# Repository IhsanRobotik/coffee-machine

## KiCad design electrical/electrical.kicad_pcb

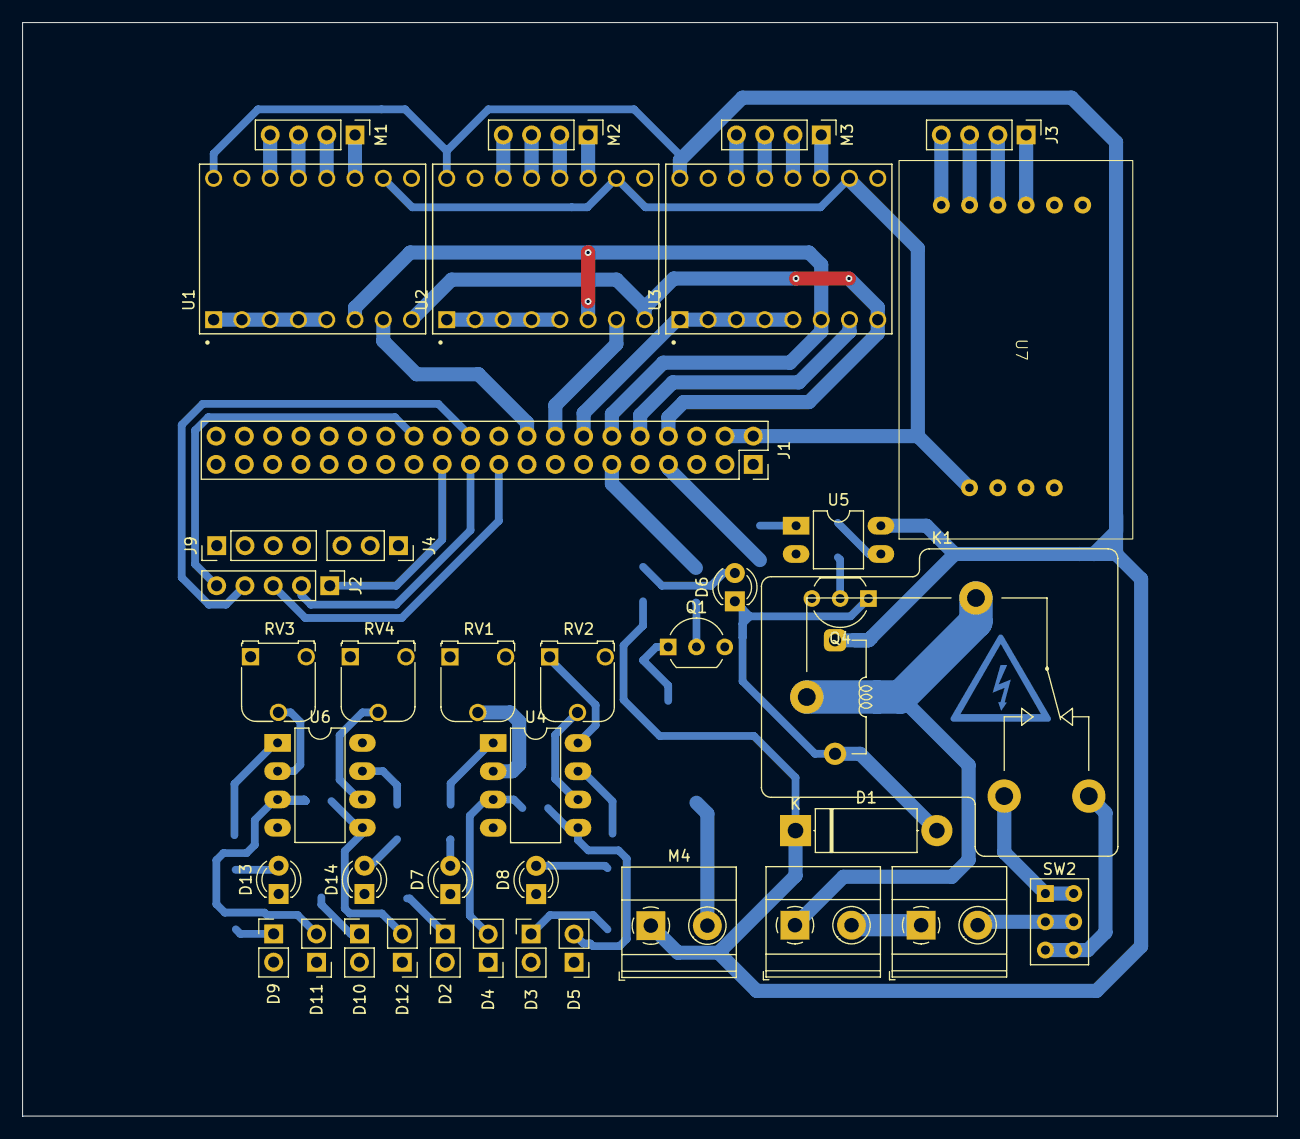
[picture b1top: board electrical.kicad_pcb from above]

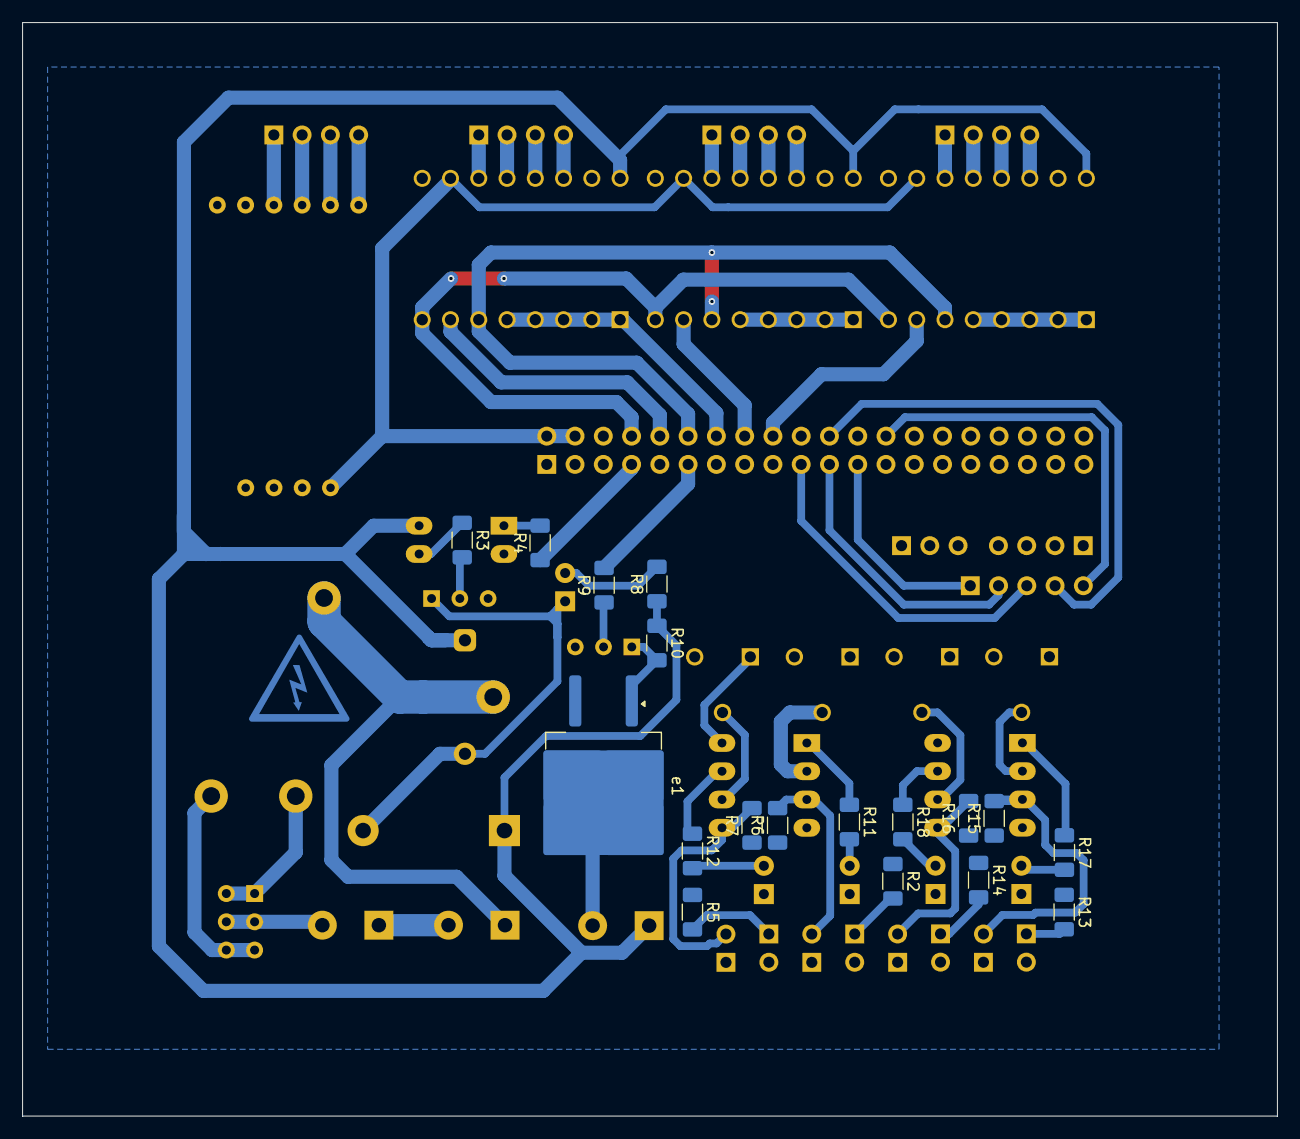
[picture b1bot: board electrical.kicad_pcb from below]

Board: 2 copper layers, 112.8 x 98.2 mm, 58 parts (18 on the bottom side), 67 nets.

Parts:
D1: 1N4007; D_5W_P12.70mm_Horizontal
D2, D3, D9, D10: IR204A; PinHeader_1x02_P2.54mm_Vertical
D4, D5, D11, D12: D_Photo; PinHeader_1x02_P2.54mm_Vertical
D6, D7, D8, D13, D14: LED; LED_D3.0mm
J1: Raspberry Pi GPIO; PinSocket_2x20_P2.54mm_Vertical
J2: Touch screen connector; PinHeader_1x05_P2.54mm_Vertical
J3: Load_cell; PinHeader_1x04_P2.54mm_Vertical
J4: PIR_sensor; PinSocket_1x03_P2.54mm_Vertical
J9: Water_sensor; PinHeader_1x04_P2.54mm_Vertical
K1: RAYEX-L90; Relay_SPDT_RAYEX-L90
M1: Milk_powder; PinHeader_1x04_P2.54mm_Vertical
M2: Instant_coffee; PinHeader_1x04_P2.54mm_Vertical
M3: Sugar; PinHeader_1x04_P2.54mm_Vertical
M4: Motor_DC; TerminalBlock_Phoenix_MKDS-1,5-2-5.08_1x02_P5.08mm_Horizont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
P1: IEC_60320_C13_Plug; TerminalBlock_Phoenix_MKDS-1,5-2-5.08_1x02_P5.08mm_Horizont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
Q1, Q4: 2N3904; TO-92_Inline_Wide
R1: Heater; TerminalBlock_Phoenix_MKDS-1,5-2-5.08_1x02_P5.08mm_Horizont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
R2, R5, R13, R14: 100; R_1206_3216Metric_Pad1.30x1.75mm_HandSolder
R3: 120; R_1206_3216Metric_Pad1.30x1.75mm_HandSolder
R4: 470; R_1206_3216Metric_Pad1.30x1.75mm_HandSolder
R6, R7, R9, R10, R15, R16: 10K; R_1206_3216Metric_Pad1.30x1.75mm_HandSolder
R8, R11, R12, R17, R18: 510; R_1206_3216Metric_Pad1.30x1.75mm_HandSolder
RV1, RV2, RV3, RV4: Pot; Potentiometer_Runtron_RM-065_Vertical
SW2: SW_SPDT; SW_NKK_G1xJP
U1, U2, U3: A4988_STEPPER_MOTOR_DRIVER_CARRIER; MODULE_A4988_STEPPER_MOTOR_DRIVER_CARRIER
U4, U6: LM358; DIP-8_W7.62mm_LongPads
U5: PC817; DIP-4_W7.62mm_LongPads
U7: HX711
e1: IRF540N; TO-263-2

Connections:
+3.3V: J1.1, J1.17
+5V: D2.2 (A), D3.2 (A), D4.1 (K), D5.1 (K), D9.2 (A), D10.2 (A), D11.1 (K), D12.1 (K), J1.2, J1.4, J4.1, J9.1, RV1.1, RV2.1, RV3.1, RV4.1, U1.10 (VDD), U2.10 (VDD), U3.10 (VDD), U4.8 (V+), U6.8 (V+), U7.4 (VCC)
+12V: D1.1 (K), K1.A1, M4.1 (+), R8.1, R10.1, U1.16 (VMOT), U2.16 (VMOT), U3.16 (VMOT), U5.4
/COFFEE: J1.35, R17.1, U6.1
/IR 2/OUT1: R11.1, U4.1
/IR 2/OUT2: R12.1, U4.7
/SUGAR: J1.37, R18.1, U6.7
AC: P1.2 (L), SW2.2 (B)
BLACK E-: J3.2, U7.8 (A+)
GND: D7.1 (K), D8.1 (K), D13.1 (K), D14.1 (K), J1.6, J1.9, J1.14, J1.20, J1.25, J1.30, J1.34, J1.39, J4.3, J9.4, R2.1, R5.1, R6.1, R7.1, R13.1, R14.1, R15.1, R16.1, RV1.3, RV2.3, RV3.3, RV4.3, U1.1 (~ENABLE), U1.2 (MS1), U1.3 (MS2), U1.4 (MS3), U1.5 (~RESET), U1.9 (GND), U1.15 (GND), U2.1 (~ENABLE), U2.2 (MS1), U2.3 (MS2), U2.4 (MS3), U2.5 (~RESET), U2.9 (GND), U2.15 (GND), U3.1 (~ENABLE), U3.2 (MS1), U3.3 (MS2), U3.4 (MS3), U3.5 (~RESET), U3.9 (GND), U3.15 (GND), U4.4 (V-), U5.2, U6.4 (V-), U7.1 (GND)
GND +12V: Q1.3 (E), Q4.3 (E), e1.3 (S)
GPIO4: J1.7, R4.1
GPIO7 SPI CE1: J1.26, J2.5
GPIO9 SPI MISO: J1.21, J2.2
GPIO10 SPI MOSI: J1.19, J2.3
GPIO11 SPI SCLK: J1.23, J2.1
GPIO14: J1.8, U1.8 (DIR), U2.8 (DIR), U3.8 (DIR)
GPIO15: J1.10, U3.7 (STEP)
GPIO17: J1.11, R9.2, U7.2 (DATA)
GPIO18: J1.12, U1.6 (~SLEEP), U2.6 (~SLEEP), U3.6 (~SLEEP)
GPIO23: J1.16, U2.7 (STEP)
GPIO24: J1.18, U1.7 (STEP)
GPIO25: J1.22, J2.4
GPIO27: J1.13, U7.3 (SCK)
GREEN A+: J3.4, U7.10 (B+)
NEUT: P1.1 (N), R1.2
unnamed: D1.2 (A), D6.1 (K), K1.A2, Q4.1 (C)
unnamed: D2.1 (K), R2.2
unnamed: D3.1 (K), R5.2
unnamed: D4.2 (A), R6.2, U4.3 (+)
unnamed: D5.2 (A), R7.2, U4.5 (+)
unnamed: D6.2 (A), R8.2
unnamed: D7.2 (A), R11.2
unnamed: D8.2 (A), R12.2
unnamed: D9.1 (K), R13.2
unnamed: D10.1 (K), R14.2
unnamed: D11.2 (A), R15.2, U6.3 (+)
unnamed: D12.2 (A), R16.2, U6.5 (+)
unnamed: D13.2 (A), R17.2
unnamed: D14.2 (A), R18.2
unnamed: K1.11A, K1.11B, R1.1
unnamed: M1.2 (-), U1.12 (1A)
unnamed: M2.2 (-), U2.12 (1A)
unnamed: M3.2 (-), U3.12 (1A)
unnamed: M4.2 (-), e1.2 (D)
unnamed: Q1.2 (B), R9.1
unnamed: Q1.1 (C), R10.2, e1.1 (G)
unnamed: Q4.2 (B), R3.2
unnamed: R3.1, U5.3
unnamed: R4.2, U5.1
unnamed: K1.14, SW2.1 (A)
unnamed: K1.12, SW2.3 (C)
unnamed: M1.1, U1.11 (1B)
unnamed: M1.3, U1.13 (2A)
unnamed: M1.4, U1.14 (2B)
unnamed: M2.1, U2.11 (1B)
unnamed: M2.3, U2.13 (2A)
unnamed: M2.4, U2.14 (2B)
unnamed: M3.1, U3.11 (1B)
unnamed: M3.3, U3.13 (2A)
unnamed: M3.4, U3.14 (2B)
unnamed: RV1.2, U4.2 (-)
unnamed: RV2.2, U4.6 (-)
unnamed: RV3.2, U6.2 (-)
unnamed: RV4.2, U6.6 (-)
RED E+: J3.1, U7.7 (A-)
WHITE A-: J3.3, U7.9 (B-)

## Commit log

2025-04-04 first commit from vending
2025-04-04 added qr css and format for prices
2025-04-19 added notification url
2025-04-19 changed payment verification to url callback
2025-04-25 better index ui
2025-04-25 touch screen
2025-04-28 sha512
2025-04-28 this code trash
2025-04-29 {great code}
2025-04-29 grat code! sha512 works
2025-04-29 touch swioe to scroll
2025-06-05 added adjustment
2025-06-05 added scrolling feature
2025-06-06 jello
2025-06-06 change to button from scrolling
2025-06-10 added read hx711
2025-06-10 Added hx711 c++ submodule
2025-06-10 added hx711
2025-06-16 minor changes
2025-06-16 Remove venv from tracking
2025-06-17 added heating logic
2025-06-29 i dont even know
2025-07-07 minor
2025-07-20 more changes lul
2025-07-26 vosk changes
2025-08-04 working code 5 8 2025
2025-08-05 fix ngrok
2025-08-05 added rpi control
2025-08-11 teest script
2025-08-13 sussy changes
2025-08-13 hello
2025-08-21 deleted unused code
